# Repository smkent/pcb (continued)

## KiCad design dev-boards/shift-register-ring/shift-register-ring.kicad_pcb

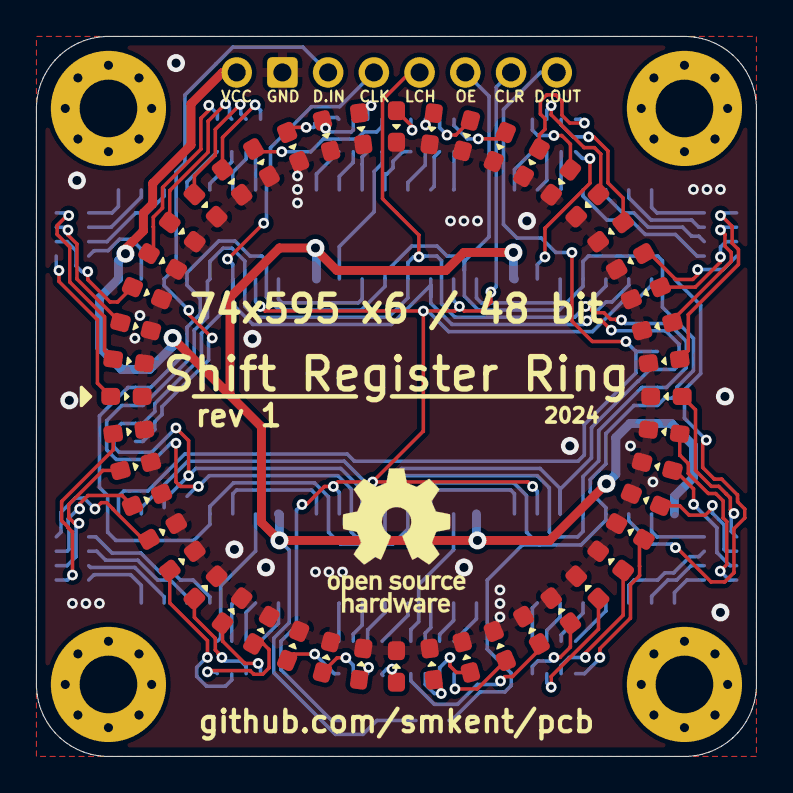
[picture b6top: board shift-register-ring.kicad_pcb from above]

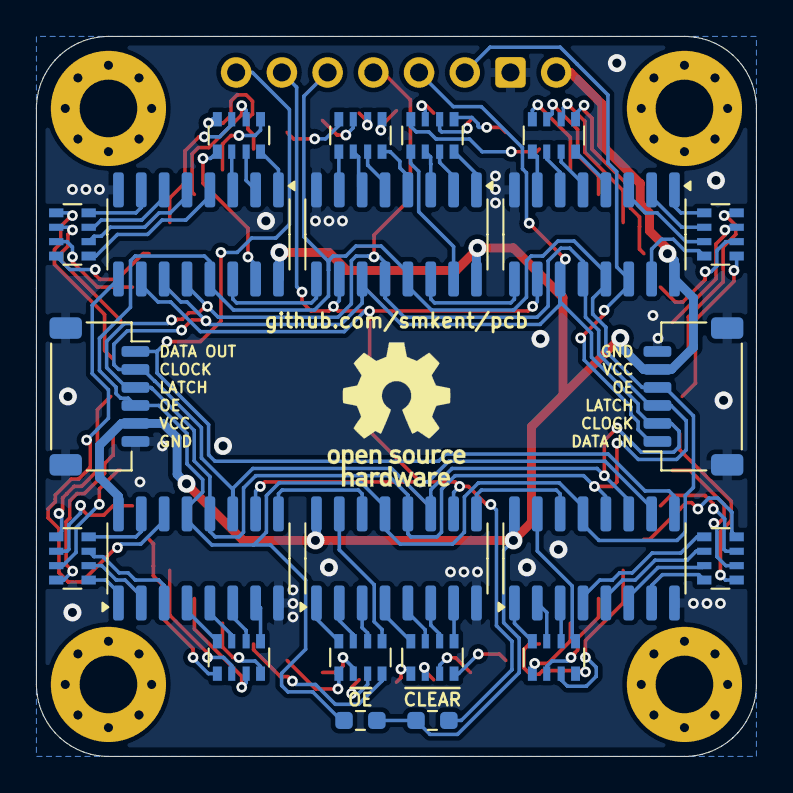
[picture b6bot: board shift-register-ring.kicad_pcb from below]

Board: 2 copper layers, 40.0 x 40.0 mm, 71 parts (23 on the bottom side), 109 nets.

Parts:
J0: Pin Headers; PinHeader_1x08_P2.54mm_Vertical_simple_pad2gnd
J2, J3: JST SH; JST_SH_SM06B-SRSS-TB_1x06-1MP_P1.00mm_Horizontal
LED1, LED2, LED3, LED4, LED5, LED6, LED7, LED8, LED9, LED10, LED11, LED12, LED13, LED14, LED15, LED16, LED17, LED18, LED19, LED20, LED21, LED22, LED23, LED24, LED25, LED26, LED27, LED28, LED29, LED30, LED31, LED32, LED33, LED34, LED35, LED36, LED37, LED38, LED39, LED40, LED41, LED42, LED43, LED44, LED45, LED46, LED47, LED48: LED; LED_0603_1608Metric_Pad1.05x0.95mm_HandSolder_simple
R1, R2: 10K; R_0603_1608Metric_Pad0.98x0.95mm_HandSolder
RN1, RN2, RN3, RN4, RN5, RN6, RN7, RN8, RN9, RN10, RN11, RN12: 10K; R_Array_Convex_4x0603
U1, U2, U3, U4, U5, U6: 74HC595; SOIC-16_3.9x9.9mm_P1.27mm

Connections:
Clear: J0.7, R1.2, U1.10 (~SRCLR), U2.10 (~SRCLR), U3.10 (~SRCLR), U4.10 (~SRCLR), U5.10 (~SRCLR), U6.10 (~SRCLR)
Clock: J0.4, J2.2, J3.2, U1.11 (SRCLK), U2.11 (SRCLK), U3.11 (SRCLK), U4.11 (SRCLK), U5.11 (SRCLK), U6.11 (SRCLK)
Data: J0.3, J2.1, U1.14 (SER)
Data2: U1.9 (QH'), U2.14 (SER)
Data3: U2.9 (QH'), U3.14 (SER)
Data4: U3.9 (QH'), U4.14 (SER)
Data5: U4.9 (QH'), U5.14 (SER)
Data6: U5.9 (QH'), U6.14 (SER)
Data_Out: J0.8, J3.1, U6.9 (QH')
GND: J0.2, J2.6, J2.MP (MountPin), J3.6, J3.MP (MountPin), LED1.1 (K), LED2.1 (K), LED3.1 (K), LED4.1 (K), LED5.1 (K), LED6.1 (K), LED7.1 (K), LED8.1 (K), LED9.1 (K), LED10.1 (K), LED11.1 (K), LED12.1 (K), LED13.1 (K), LED14.1 (K), LED15.1 (K), LED16.1 (K), LED17.1 (K), LED18.1 (K), LED19.1 (K), LED20.1 (K), LED21.1 (K), LED22.1 (K), LED23.1 (K), LED24.1 (K), LED25.1 (K), LED26.1 (K), LED27.1 (K), LED28.1 (K), LED29.1 (K), LED30.1 (K), LED31.1 (K), LED32.1 (K), LED33.1 (K), LED34.1 (K), LED35.1 (K), LED36.1 (K), LED37.1 (K), LED38.1 (K), LED39.1 (K), LED40.1 (K), LED41.1 (K), LED42.1 (K), LED43.1 (K), LED44.1 (K), LED45.1 (K), LED46.1 (K), LED47.1 (K), LED48.1 (K), U1.8 (GND), U2.8 (GND), U3.8 (GND), U4.8 (GND), U5.8 (GND), U6.8 (GND)
LED1: RN1.8 (R1.2), U1.15 (QA)
LED2: RN1.5 (R4.2), U1.1 (QB)
LED3: RN1.6 (R3.2), U1.2 (QC)
LED4: RN1.7 (R2.2), U1.3 (QD)
LED5: RN2.8 (R1.2), U1.4 (QE)
LED6: RN2.7 (R2.2), U1.5 (QF)
LED7: RN2.6 (R3.2), U1.6 (QG)
LED8: RN2.5 (R4.2), U1.7 (QH)
LED9: RN3.5 (R4.2), U2.15 (QA)
LED10: RN3.8 (R1.2), U2.1 (QB)
LED11: RN3.7 (R2.2), U2.2 (QC)
LED12: RN3.6 (R3.2), U2.3 (QD)
LED13: RN4.8 (R1.2), U2.4 (QE)
LED14: RN4.7 (R2.2), U2.5 (QF)
LED15: RN4.6 (R3.2), U2.6 (QG)
LED16: RN4.5 (R4.2), U2.7 (QH)
LED17: RN5.5 (R4.2), U3.15 (QA)
LED18: RN5.8 (R1.2), U3.1 (QB)
LED19: RN5.7 (R2.2), U3.2 (QC)
LED20: RN5.6 (R3.2), U3.3 (QD)
LED21: RN6.5 (R4.2), U3.4 (QE)
LED22: RN6.6 (R3.2), U3.5 (QF)
LED23: RN6.7 (R2.2), U3.6 (QG)
LED24: RN6.8 (R1.2), U3.7 (QH)
LED25: RN7.8 (R1.2), U4.15 (QA)
LED26: RN7.5 (R4.2), U4.1 (QB)
LED27: RN7.6 (R3.2), U4.2 (QC)
LED28: RN7.7 (R2.2), U4.3 (QD)
LED29: RN8.8 (R1.2), U4.4 (QE)
LED30: RN8.7 (R2.2), U4.5 (QF)
LED31: RN8.6 (R3.2), U4.6 (QG)
LED32: RN8.5 (R4.2), U4.7 (QH)
LED33: RN9.5 (R4.2), U5.15 (QA)
LED34: RN9.8 (R1.2), U5.1 (QB)
LED35: RN9.7 (R2.2), U5.2 (QC)
LED36: RN9.6 (R3.2), U5.3 (QD)
LED37: RN10.8 (R1.2), U5.4 (QE)
LED38: RN10.7 (R2.2), U5.5 (QF)
LED39: RN10.6 (R3.2), U5.6 (QG)
LED40: RN10.5 (R4.2), U5.7 (QH)
LED41: RN11.5 (R4.2), U6.15 (QA)
LED42: RN11.8 (R1.2), U6.1 (QB)
LED43: RN11.7 (R2.2), U6.2 (QC)
LED44: RN11.6 (R3.2), U6.3 (QD)
LED45: RN12.5 (R4.2), U6.4 (QE)
LED46: RN12.6 (R3.2), U6.5 (QF)
LED47: RN12.7 (R2.2), U6.6 (QG)
LED48: RN12.8 (R1.2), U6.7 (QH)
Latch: J0.5, J2.3, J3.3, U1.12 (RCLK), U2.12 (RCLK), U3.12 (RCLK), U4.12 (RCLK), U5.12 (RCLK), U6.12 (RCLK)
unnamed: LED1.2 (A), RN1.1 (R1.1)
unnamed: LED2.2 (A), RN1.4 (R4.1)
unnamed: LED3.2 (A), RN1.3 (R3.1)
unnamed: LED4.2 (A), RN1.2 (R2.1)
unnamed: LED5.2 (A), RN2.1 (R1.1)
unnamed: LED6.2 (A), RN2.2 (R2.1)
unnamed: LED7.2 (A), RN2.3 (R3.1)
unnamed: LED8.2 (A), RN2.4 (R4.1)
unnamed: LED9.2 (A), RN3.4 (R4.1)
unnamed: LED10.2 (A), RN3.1 (R1.1)
unnamed: LED11.2 (A), RN3.2 (R2.1)
unnamed: LED12.2 (A), RN3.3 (R3.1)
unnamed: LED13.2 (A), RN4.1 (R1.1)
unnamed: LED14.2 (A), RN4.2 (R2.1)
unnamed: LED15.2 (A), RN4.3 (R3.1)
unnamed: LED16.2 (A), RN4.4 (R4.1)
unnamed: LED17.2 (A), RN5.4 (R4.1)
unnamed: LED18.2 (A), RN5.1 (R1.1)
unnamed: LED19.2 (A), RN5.2 (R2.1)
unnamed: LED20.2 (A), RN5.3 (R3.1)
unnamed: LED21.2 (A), RN6.4 (R4.1)
unnamed: LED22.2 (A), RN6.3 (R3.1)
unnamed: LED23.2 (A), RN6.2 (R2.1)
unnamed: LED24.2 (A), RN6.1 (R1.1)
unnamed: LED25.2 (A), RN7.1 (R1.1)
unnamed: LED26.2 (A), RN7.4 (R4.1)
unnamed: LED27.2 (A), RN7.3 (R3.1)
unnamed: LED28.2 (A), RN7.2 (R2.1)
unnamed: LED29.2 (A), RN8.1 (R1.1)
unnamed: LED30.2 (A), RN8.2 (R2.1)
unnamed: LED31.2 (A), RN8.3 (R3.1)
unnamed: LED32.2 (A), RN8.4 (R4.1)
unnamed: LED33.2 (A), RN9.4 (R4.1)
unnamed: LED34.2 (A), RN9.1 (R1.1)
unnamed: LED35.2 (A), RN9.2 (R2.1)
unnamed: LED36.2 (A), RN9.3 (R3.1)
unnamed: LED37.2 (A), RN10.1 (R1.1)
unnamed: LED38.2 (A), RN10.2 (R2.1)
unnamed: LED39.2 (A), RN10.3 (R3.1)
unnamed: LED40.2 (A), RN10.4 (R4.1)
unnamed: LED41.2 (A), RN11.4 (R4.1)
unnamed: LED42.2 (A), RN11.1 (R1.1)
unnamed: LED43.2 (A), RN11.2 (R2.1)
unnamed: LED44.2 (A), RN11.3 (R3.1)
unnamed: LED45.2 (A), RN12.4 (R4.1)
unnamed: LED46.2 (A), RN12.3 (R3.1)
unnamed: LED47.2 (A), RN12.2 (R2.1)
unnamed: LED48.2 (A), RN12.1 (R1.1)
OE: J0.6, J2.4, J3.4, R2.2, U1.13 (~OE), U2.13 (~OE), U3.13 (~OE), U4.13 (~OE), U5.13 (~OE), U6.13 (~OE)
VCC: J0.1, J2.5, J3.5, R1.1, R2.1, U1.16 (VCC), U2.16 (VCC), U3.16 (VCC), U4.16 (VCC), U5.16 (VCC), U6.16 (VCC)
